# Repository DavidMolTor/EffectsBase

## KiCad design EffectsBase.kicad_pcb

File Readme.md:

# EFFECTS BASE

Guitar effects platform for interfacing with mini PCIe based boards.

## Introduction

This project consists of a platform with all the controls and signal management for mini PCIe board-based guitar effects.

The platform contains a total of 4 potentiometers and 4 SPDT switches that are accessible throught he mini PCIe connector.

For powering, it offers high filtering and a charge pump in order to produce a negative supply rail.

## Features

 - Mini PCIe connector

- Charge pump inverter

 - 4 potentiometers

 - 4 SPDT switches

 - True bypass

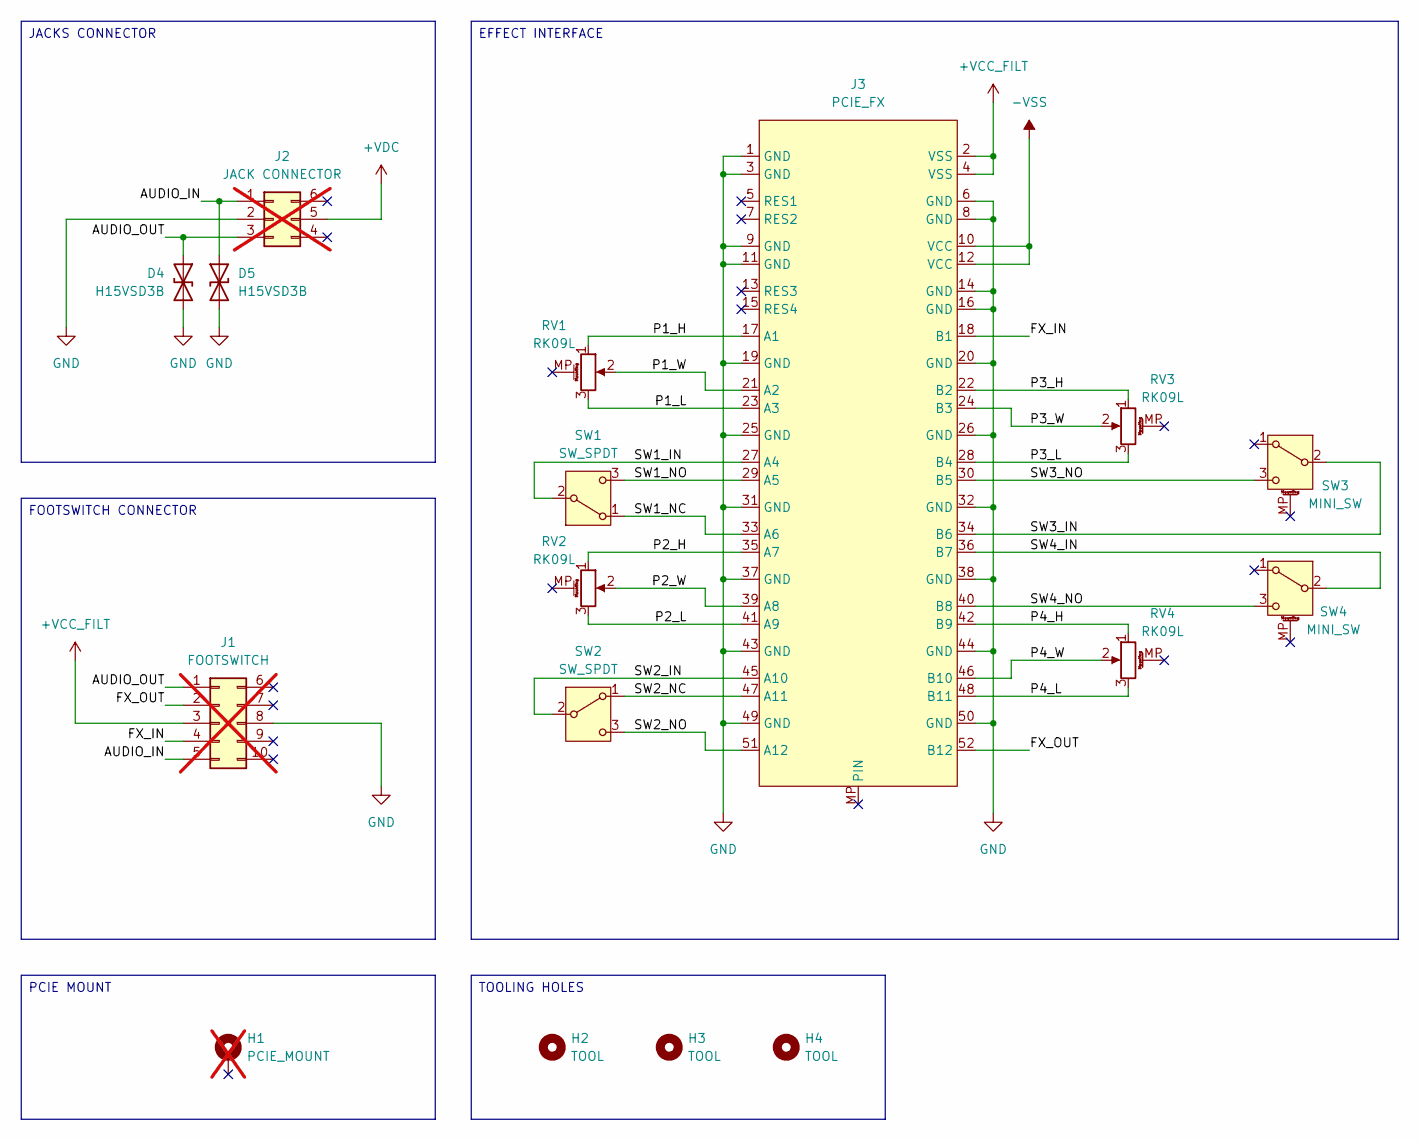
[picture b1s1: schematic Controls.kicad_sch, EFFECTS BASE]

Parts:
D4, D5: H15VSD3B; D_SOD-323; Manufacturer Part H15VSD3B; JLCPCB Part C20615814
H1: PCIE_MOUNT; Mounting_Wuerth_WA-SMSI-M2.5_H1.5mm_9774015151; not fitted
H2, H3, H4: TOOL; ToolingHole_1.152mm
J1: FOOTSWITCH; HEADER_THROUGH_2x05_P2.54mm; not fitted
J2: JACK CONNECTOR; HEADER_THROUGH_2x03_P2.54mm; not fitted
J3: PCIE_FX; Mini PCI_Express_Pads; Manufacturer Part 91304-99-052R2; JLCPCB Part C404126
RV1, RV2, RV3, RV4: RK09L; POT_SINGLE_VERTICAL_6X15
SW1, SW2: SW_SPDT
SW3, SW4: MINI_SW; MINI_TOGGLE_SHIELD

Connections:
+VCC_FILT: J1.3, J3.2 (VSS), J3.4 (VSS); also elsewhere on the board
+VDC: J2.5; also elsewhere on the board
-VSS: J3.10 (VCC), J3.12 (VCC); also elsewhere on the board
/Controls/AUDIO_IN: D5.1 (A1), J1.5, J2.1
/Controls/AUDIO_OUT: D4.1 (A1), J1.1, J2.3
/Controls/FX_IN: J1.4, J3.18 (B1)
/Controls/FX_OUT: J1.2, J3.52 (B12)
/Controls/P1_H: J3.17 (A1), RV1.1
/Controls/P1_L: J3.23 (A3), RV1.3
/Controls/P1_W: J3.21 (A2), RV1.2
/Controls/P2_H: J3.35 (A7), RV2.1
/Controls/P2_L: J3.41 (A9), RV2.3
/Controls/P2_W: J3.39 (A8), RV2.2
/Controls/P3_H: J3.22 (B2), RV3.1
/Controls/P3_L: J3.28 (B4), RV3.3
/Controls/P3_W: J3.24 (B3), RV3.2
/Controls/P4_H: J3.42 (B9), RV4.1
/Controls/P4_L: J3.48 (B11), RV4.3
/Controls/P4_W: J3.46 (B10), RV4.2
/Controls/SW1_IN: J3.27 (A4), SW1.2 (B)
/Controls/SW1_NC: J3.33 (A6), SW1.1 (A)
/Controls/SW1_NO: J3.29 (A5), SW1.3 (C)
/Controls/SW2_IN: J3.45 (A10), SW2.2 (B)
/Controls/SW2_NC: J3.47 (A11), SW2.1 (A)
/Controls/SW2_NO: J3.51 (A12), SW2.3 (C)
/Controls/SW3_IN: J3.34 (B6), SW3.2 (B)
/Controls/SW3_NO: J3.30 (B5), SW3.3 (C)
/Controls/SW4_IN: J3.36 (B7), SW4.2 (B)
/Controls/SW4_NO: J3.40 (B8), SW4.3 (C)
GND: D4.2 (A2), D5.2 (A2), J1.8, J2.2, J3.1 (GND), J3.3 (GND), J3.6 (GND), J3.8 (GND), J3.9 (GND), J3.11 (GND), J3.14 (GND), J3.16 (GND), J3.19 (GND), J3.20 (GND), J3.25 (GND), J3.26 (GND), J3.31 (GND), J3.32 (GND), J3.37 (GND), J3.38 (GND), J3.43 (GND), J3.44 (GND), J3.49 (GND), J3.50 (GND); also elsewhere on the board

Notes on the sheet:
TOOLING HOLES
FOOTSWITCH CONNECTOR
PCIE MOUNT
EFFECT INTERFACE
JACKS CONNECTOR

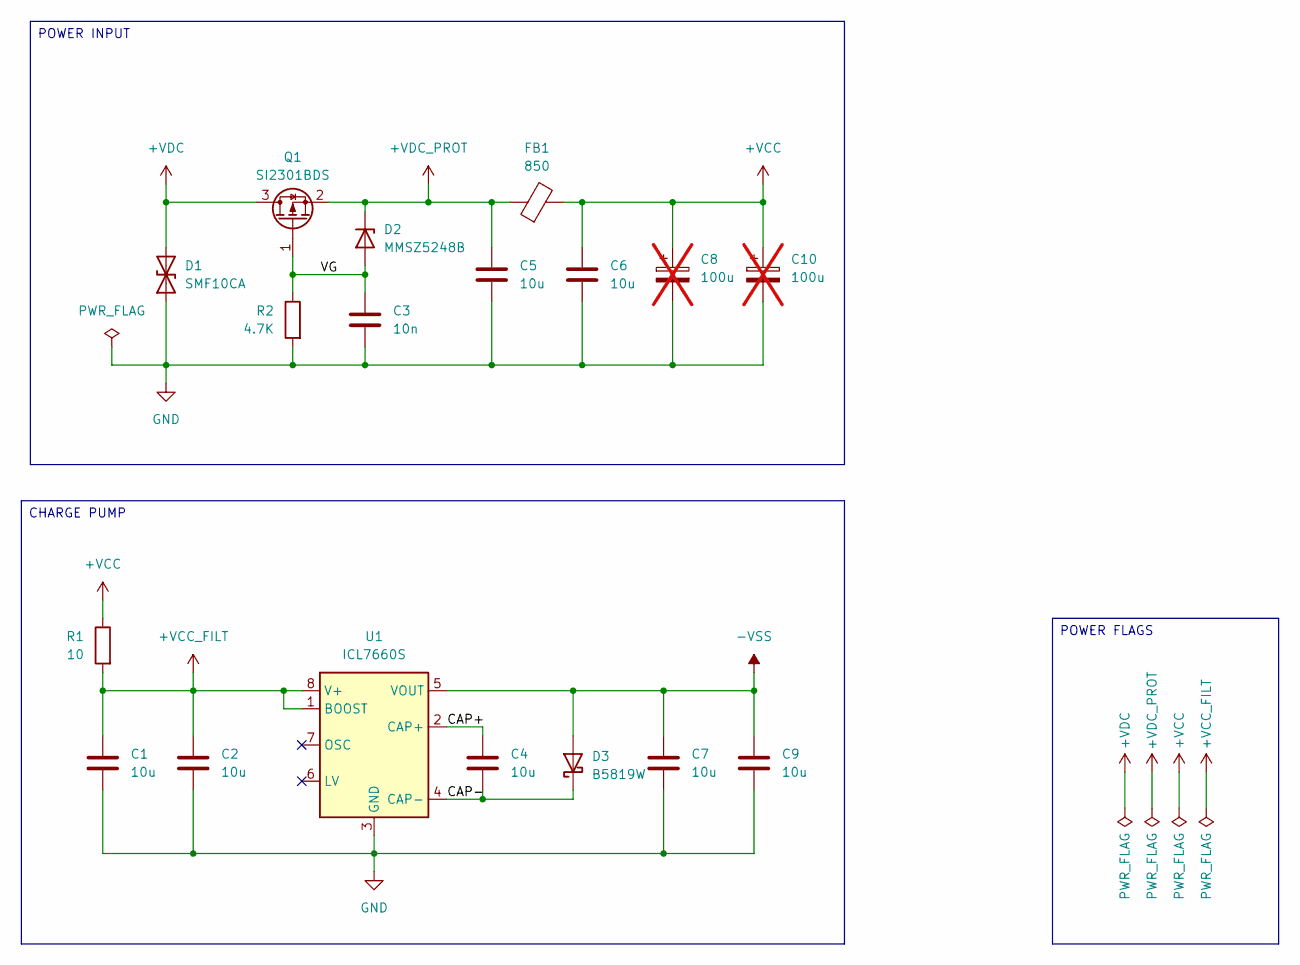
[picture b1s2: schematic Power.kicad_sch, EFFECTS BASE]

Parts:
C1, C2, C4, C5, C6, C7, C9: 10u; C_0805_2012Metric; Manufacturer Part CL21A106KAYNNNE; JLCPCB Part C15850
C3: 10n; C_0603_1608Metric; Manufacturer Part 0603B103K500NT; JLCPCB Part C57112
C8, C10: 100u; CP_Elec_6.3x5.8; Manufacturer Part HV1E107M0605PZ; JLCPCB Part C5246539; not fitted
D1: SMF10CA; D_SOD-123F; Manufacturer Part SMF10CA; JLCPCB Part C19077505
D2: MMSZ5248B; D_SOD-323; Manufacturer Part MMSZ5248BS; JLCPCB Part C22395566
D3: B5819W; D_SOD-123; Manufacturer Part B5819W SL; JLCPCB Part C8598
FB1: 850; L_0603_1608Metric; Manufacturer Part SDCL1608C68NJTDF; JLCPCB Part C13415
Q1: SI2301BDS; SOT-23; Manufacturer Part SI2301CDS-T1-GE3; JLCPCB Part C10487
R1: 10; R_0603_1608Metric; Manufacturer Part 0603WAF1000T5E; JLCPCB Part C22775
R2: 4.7K; R_0603_1608Metric; Manufacturer Part 0603WAF4701T5E; JLCPCB Part C23162
U1: ICL7660S; SOIC-8_3.9x4.9mm_P1.27mm; Manufacturer Part ICL7660SIBAZT; JLCPCB Part C7535

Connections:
+VCC: C6.1, C8.1, C10.1, FB1.2, R1.1
+VCC_FILT: C1.1, C2.1, R1.2, U1.1 (BOOST), U1.8 (V+); also elsewhere on the board
+VDC: D1.2 (A2), Q1.3 (D); also elsewhere on the board
+VDC_PROT: C5.1, D2.1 (K), FB1.1, Q1.2 (S)
-VSS: C7.1, C9.1, D3.2 (A), U1.5 (VOUT); also elsewhere on the board
/Power/CAP+: C4.1, U1.2 (CAP+)
/Power/CAP-: C4.2, D3.1 (K), U1.4 (CAP-)
/Power/VG: C3.1, D2.2 (A), Q1.1 (G), R2.1
GND: C1.2, C2.2, C3.2, C5.2, C6.2, C7.2, C8.2, C9.2, C10.2, D1.1 (A1), R2.2, U1.3 (GND); also elsewhere on the board

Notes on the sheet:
CHARGE PUMP
POWER INPUT
POWER FLAGS

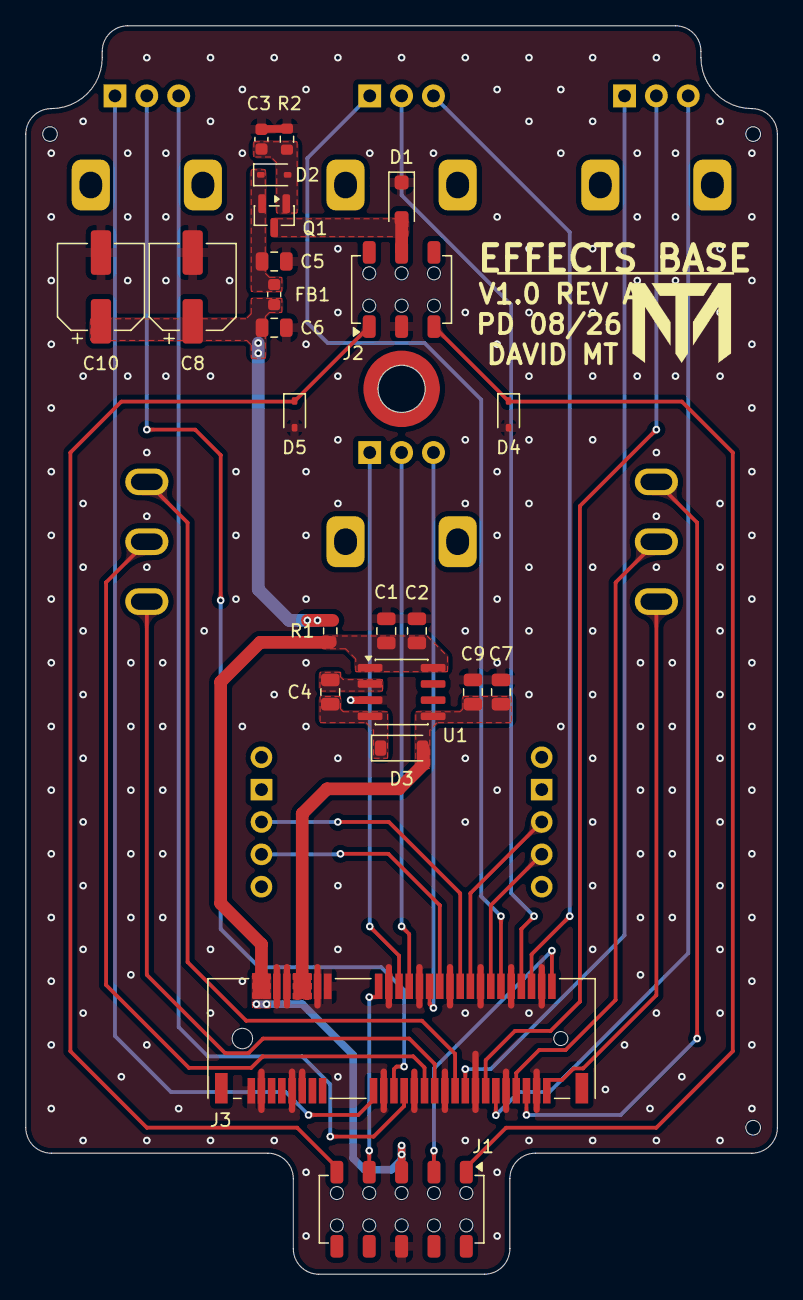
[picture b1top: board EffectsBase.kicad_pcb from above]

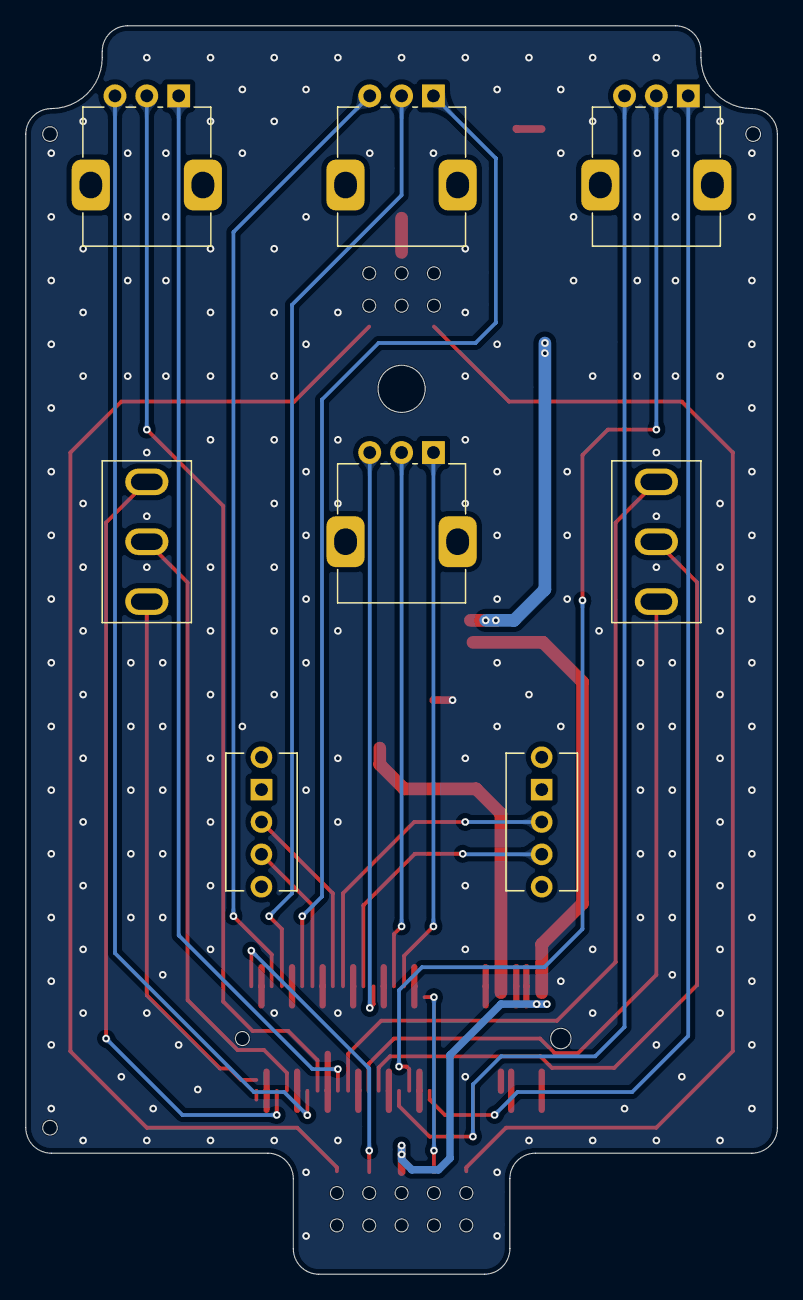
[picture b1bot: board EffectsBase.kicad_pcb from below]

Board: 2 copper layers, 59.0 x 98.0 mm, 35 parts (8 on the bottom side), 35 nets.

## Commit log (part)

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2026-04-20 Initial files
    Added the initial repository files.
2026-04-20 Description file
    Added a readme file.
2026-04-20 Project files
    Added the initial project files.
2026-04-22 Initial schematic
    Finished the base schematic.
    Included all the controls and updated the power supply.
2026-04-25 Initial layout
    Finished the initial PCB layout.
2026-04-29 Filtering section and layout
    Updated the PCB layout.
    Added additional input voltage filtering.
2026-04-29 Charge pump layout
    Added the layout for the charge pump.
2026-04-29 Control layout
    Updated the layout for the controls.
2026-04-30 Board layout
    Updated the layout of the power lines.
    Updated the layout of the control signals.
2026-05-01 Layout and mounting
    Connected all tracks in the layout.
    Added a mounting standoff.
2026-05-02 Finished layout
    Initial PCB layout iteration.
    Updated the readme file.
    Added board images.
    Added output files.
